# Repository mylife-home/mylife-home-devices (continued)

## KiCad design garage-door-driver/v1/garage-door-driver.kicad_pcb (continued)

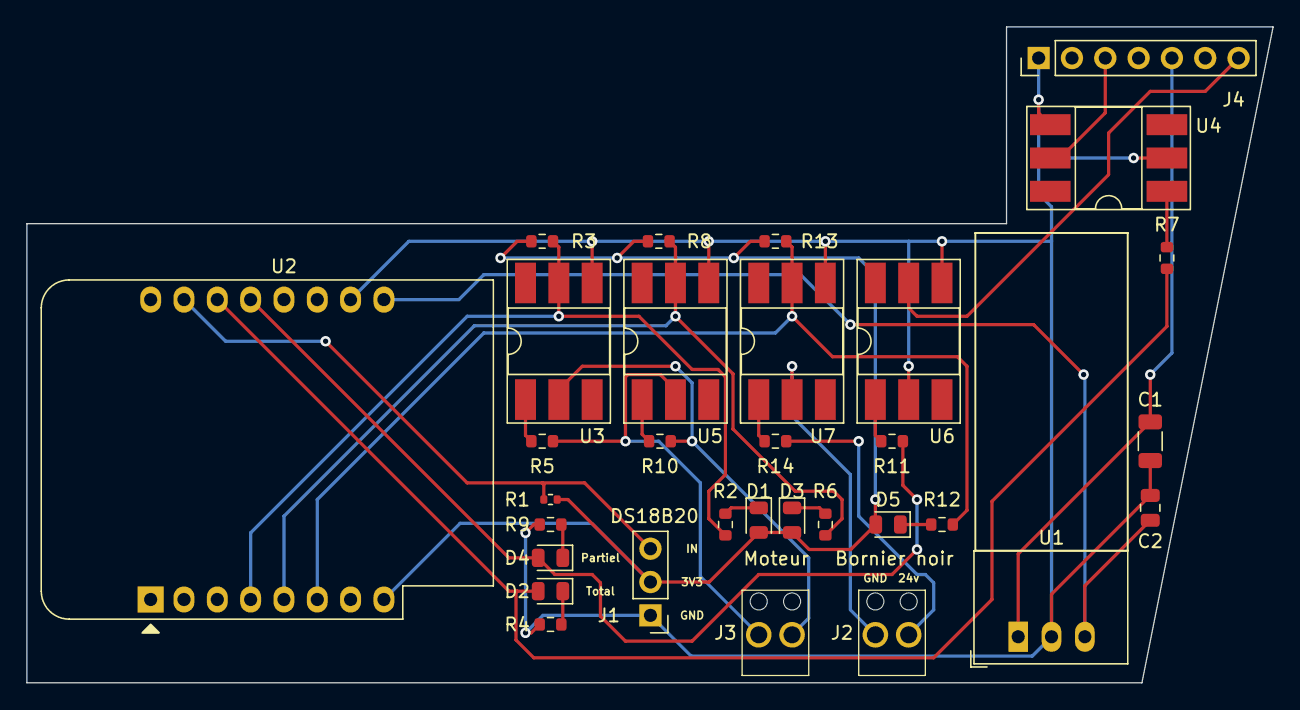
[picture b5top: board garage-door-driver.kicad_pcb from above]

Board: 2 copper layers, 95.0 x 50.0 mm, 32 parts (0 on the bottom side), 26 nets.

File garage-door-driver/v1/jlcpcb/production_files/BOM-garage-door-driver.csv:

Comment,Designator,Footprint,LCSC
2.2KΩ,"R10,R14,R5",R_0603_1608Metric,C176136
1KΩ,"R12,R2,R4,R6,R9",R_0603_1608Metric,C21190
220Ω,"R11,R7",R_0603_1608Metric,C22962
LED,"D1,D2,D3,D4,D5",D_0805_2012Metric,C2297
10KΩ,"R13,R3,R8",R_0603_1608Metric,C25804
4.7KΩ,R1,R_0402_1005Metric,C25900
10μF/50V,C1,C_1206_3216Metric,C417124
4N35,"U3,U4,U5,U6,U7",DIP-6_W8.89mm_SMDSocket_LongPads,C500385
22μF/10V,C2,C_0805_2012Metric,C92814
Conn_01x03_Male,J1,PinHeader_1x03_P2.54mm_Vertical,
WeMos_D1_mini,U2,WEMOS_D1_mini_light,
Conn_01x07_Pin,J4,PinHeader_1x07_P2.54mm_Vertical,
Screw_Terminal_01x02,J2,RS PRO Terminal Small x2,
R-785.0-1.0,U1,Converter_DCDC_RECOM_R-78E-0.5_THT,
Screw_Terminal_01x02,J3,RS PRO Terminal Small x2,

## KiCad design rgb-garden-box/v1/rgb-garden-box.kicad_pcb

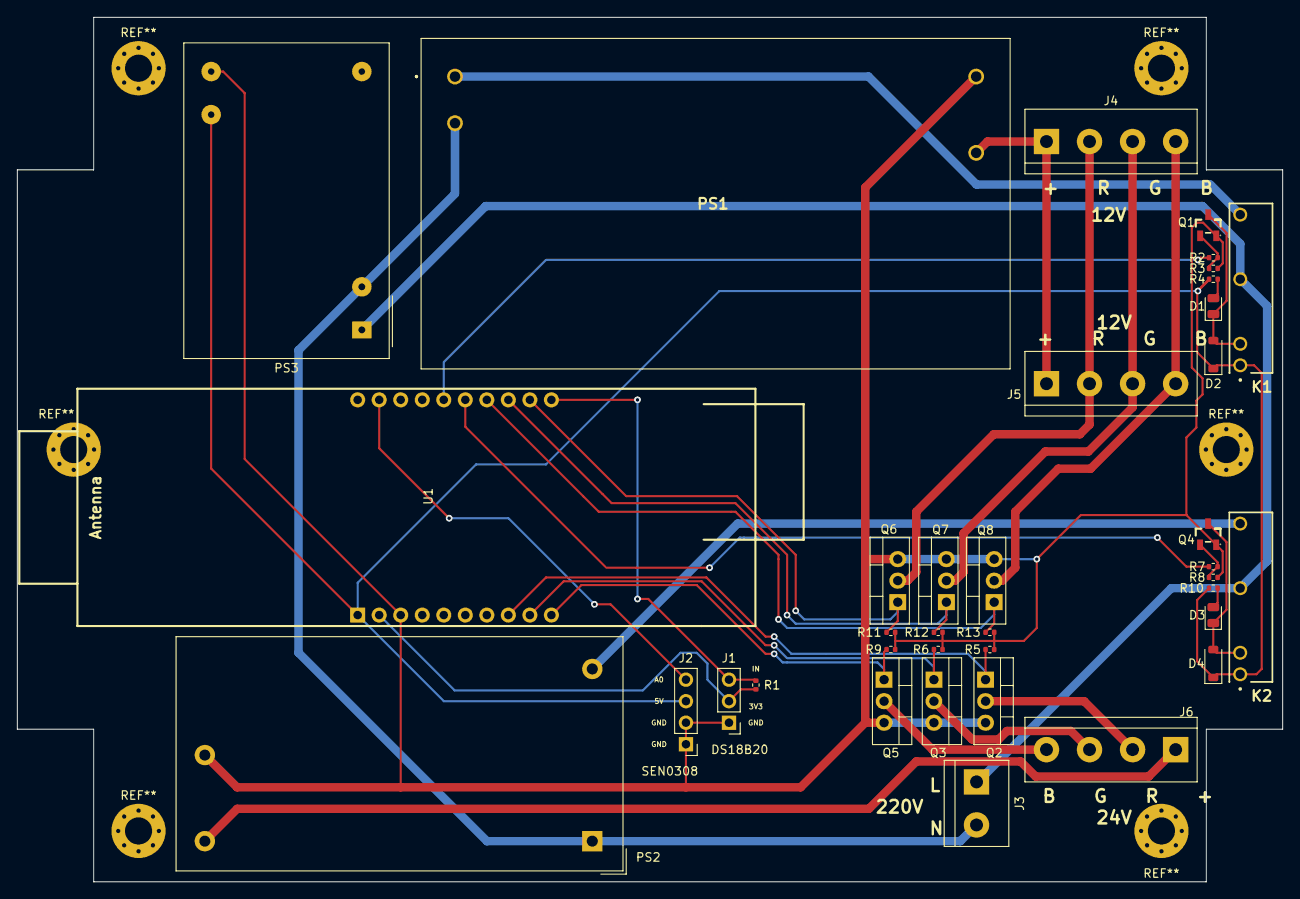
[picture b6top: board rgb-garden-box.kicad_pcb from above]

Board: 2 copper layers, 149.3 x 102.0 mm, 37 parts (0 on the bottom side), 31 nets.

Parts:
D1, D3: LED; D_0805_2012Metric
D2, D4: 1N4148; D_SOD-123
J1: Conn_01x03_Male; PinHeader_1x03_P2.54mm_Vertical
J2: Conn_01x04_Male; PinHeader_1x04_P2.54mm_Vertical
J3: Screw_Terminal_01x02; TerminalBlock_bornier-2_P5.08mm
J4, J5, J6: Screw_Terminal_01x04; TerminalBlock_bornier-4_P5.08mm
K1, K2: G6DN-1A-L_DC5; G6DN-1A-L
PS1: Mean Well 12V 2.5A (30W); IRM-30-12
PS2: RS PRO 24V 833mA (20W); RS PRO Alim 5V 2A
PS3: Alim RS PRO 5V 1A; Converter_ACDC_MeanWell_IRM-03-xx_THT
Q1, Q4: 2N3904; SOT-23-3_L2.9-W1.3-P1.90-LS2.4-TR
Q2, Q3, Q5, Q6, Q7, Q8: IRLZ44N; TO-220-3_Vertical
R1: 4.7KΩ; R_0402_1005Metric
R2, R4, R7, R10: 1KΩ; R_0402_1005Metric
R3, R5, R6, R8, R9, R11, R12, R13: 10KΩ; R_0402_1005Metric
U1: ESP32-POE

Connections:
+3V3: J1.2, R1.1, U1.2 (+3.3V_(out))
+5V: D2.1 (K), D4.1 (K), J2.3, K1.1, K2.1, PS3.16 (+Vo), R4.1, R10.1, U1.1 (+5V)
+12V: J4.1, J5.1, PS1.3 (+Vout)
+24V: J6.1, PS2.4 (+Vo)
GND: J1.1, J2.1, J2.2, PS1.4 (-Vout), PS2.3 (-Vo), PS3.14 (-Vo), Q1.1 (E), Q2.3 (S), Q3.3 (S), Q4.1 (E), Q5.3 (S), Q6.3 (S), Q7.3 (S), Q8.3 (S), R3.2, R5.2, R6.2, R8.2, R9.2, R11.2, R12.2, R13.2, U1.3 (GND)
unnamed: D1.2 (A), R4.2
unnamed: D1.1 (K), D2.2 (A), K1.2, Q1.3 (C)
unnamed: D3.2 (A), R10.2
unnamed: D3.1 (K), D4.2 (A), K2.2, Q4.3 (C)
unnamed: J1.3, R1.2, U1.11 (GPIO13)
unnamed: J2.4, U1.19 (GPIO36)
unnamed: J3.1, K1.5, K2.5, PS3.1 (AC/L)
unnamed: J3.2, PS1.2 (AC/N), PS2.1 (AC/N), PS3.3 (AC/N)
unnamed: J4.2, J5.2, Q6.2 (D)
unnamed: J4.3, J5.3, Q7.2 (D)
unnamed: J4.4, J5.4, Q8.2 (D)
unnamed: J6.2, Q2.2 (D)
unnamed: J6.3, Q3.2 (D)
unnamed: J6.4, Q5.2 (D)
unnamed: K1.8, PS1.1 (AC/L)
unnamed: K2.8, PS2.2 (AC/L)
unnamed: Q1.2 (B), R2.1, R3.1
unnamed: Q2.1 (G), R5.1, U1.8 (GPIO3)
unnamed: Q3.1 (G), R6.1, U1.9 (GPIO4)
unnamed: Q4.2 (B), R7.1, R8.1
unnamed: Q5.1 (G), R9.1, U1.10 (GPIO5)
unnamed: Q6.1 (G), R11.1, U1.12 (GPIO14)
unnamed: Q7.1 (G), R12.1, U1.13 (GPIO15)
unnamed: Q8.1 (G), R13.1, U1.14 (GPIO16)
unnamed: R7.2, U1.15 (GPIO32)
unnamed: R2.2, U1.16 (GPIO33)

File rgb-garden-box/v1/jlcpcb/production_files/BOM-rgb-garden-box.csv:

Comment,Designator,Footprint,LCSC
1KΩ,"R10,R2,R4,R7",R_0402_1005Metric,C11702
2N3904,"Q1,Q4",SOT-23-3_L2.9-W1.3-P1.90-LS2.4-TR,C18536
LED,"D1,D3",D_0805_2012Metric,C2297
10KΩ,"R11,R12,R13,R3,R5,R6,R8,R9",R_0402_1005Metric,C25744
4.7KΩ,R1,R_0402_1005Metric,C25900
1N4148,"D2,D4",D_SOD-123,C81598
IRLZ44N,Q8,TO-220-3_Vertical,
IRLZ44N,Q7,TO-220-3_Vertical,
IRLZ44N,Q6,TO-220-3_Vertical,
IRLZ44N,Q5,TO-220-3_Vertical,
IRLZ44N,Q3,TO-220-3_Vertical,
IRLZ44N,Q2,TO-220-3_Vertical,
G6DN-1A-L_DC5,K1,G6DN-1A-L,
Screw_Terminal_01x04,J5,TerminalBlock_bornier-4_P5.08mm,
Screw_Terminal_01x04,J6,TerminalBlock_bornier-4_P5.08mm,
Mean Well 12V 2.5A (30W),PS1,IRM-30-12,
G6DN-1A-L_DC5,K2,G6DN-1A-L,
Conn_01x03_Male,J1,PinHeader_1x03_P2.54mm_Vertical,
Screw_Terminal_01x04,J4,TerminalBlock_bornier-4_P5.08mm,
Screw_Terminal_01x02,J3,TerminalBlock_bornier-2_P5.08mm,
RS PRO 24V 833mA (20W),PS2,RS PRO Alim 5V 2A,
ESP32-POE,U1,ESP32-POE,
Alim RS PRO 5V 1A,PS3,Converter_ACDC_MeanWell_IRM-03-xx_THT,
Conn_01x04_Male,J2,PinHeader_1x04_P2.54mm_Vertical,

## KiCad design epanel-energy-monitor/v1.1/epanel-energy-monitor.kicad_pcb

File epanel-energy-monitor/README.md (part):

# ePanel Energy Monitor

## Besoin

- 12 capteurs
  - abonnement 12KVA ~ 55A
  - 4 sur inter diff (entre 40A et 63A)
  - 8 sur disjoncteurs (entre 10A et 32A)
- teleinfo

## Design

- MCP3208 x2
- déplacer ESP dans un boitier DIN a part

### Matériel

- Boîtier : 
  - https://fr.rs-online.com/web/p/boitiers-rail-din/7495837
  - https://fr.farnell.com/camdenboss/cnmb-6-kit/boitier-rail-din-m6/dp/3954259
- Borniers :
  - Petits : https://fr.rs-online.com/web/p/borniers-pour-circuits-imprimes/7901098
  - Grands : https://fr.rs-online.com/web/p/borniers-pour-circuits-imprimes/1444286
- Selecteurs : 
  - https://fr.rs-online.com/web/p/interrupteurs-dip-de-codage-rotatif/1796751
  - https://fr.farnell.com/nidec-copal/ss-10-15spe/commut-rotatif-sp5t-0-1a-5vdc/dp/2854806
- Câble 2x4 : https://www.amazon.fr/sourcing-map-Connecteur-Broche-Femelle/dp/B07H26VF1J
- Transfo : https://fr.rs-online.com/web/p/transformateurs-pour-circuits-imprimes/7320525
-  CT Clamp Schneider:
  - https://www.amazon.fr/Transformateurs-courant-ferm%C3%A9s-80a-Lot/dp/B01G5M1MT4
  - https://www.se.com/fr/fr/product/EER39200/wiser-energy-lot-de-5-tc-transformateurs-de-courant-ferm%C3%A9s-80a/

## V1.1

### Réglages

- pos1 = 220Ω = 10A
- pos2 = 120Ω = 16A
- pos3 = 100Ω = 20A
- pos4 =  62Ω = 32A
- pos5 =  33Ω = 60A

### 3D view

### Main

### CT Sensor

### Images

| | | |
|---|---|---|
||||
||||
||||

### Notes:

- plus de résistances 200Ω en stock, donc remplacement par une 220Ω. L'intensité max pour 10A pass de 10.5 à 9.5

## V1

### Réglages

- pos1 = 200Ω = 10A
- pos2 = 120Ω = 16A
- pos3 = 100Ω = 20A
- pos4 =  62Ω = 32A
- pos5 =  33Ω = 60A

### 3D view

### Main

### CT Sensor

### TODO

- OK LTV-814 : mauvais footprint, le bon est plus "écarté", cf jlcpcb/parts
- OK BSS138: mauvais pinout/footprint, cf jlcpcb/parts
- OK borniers pour CT plus petits (2.54 ecartement) -> https://fr.rs-online.com/web/p/borniers-pour-circuits-imprimes/7901098
- OK transfo: pastilles bien placées mais trop petites
- OK transfo: ajouter des pin headers sur secondaire pour facilement pouvoir mesurer la tension au voltmetre
- OK Au lieu de jumpers pour config resistances, mettre un commutateur rotatif :
  - https://fr.rs-online.com/web/p/interrupteurs-dip-de-codage-rotatif/1796751
  - https://fr.farnell.com/nidec-copal/ss-10-15spe/commut-rotatif-sp5t-0-1a-5vdc/dp/2854806
- Note: Boitier DIN : Largeur espace pour bornier : 1.3cm
- OK ajouter une led pour montrer qu'il est bien alimenté

### Bugs

- pinout SS-10 KO !!!
```
1 pos3       5 NC
2 pos2       6 C
3 C          7 pos5
4 pos1       8 pos4
```
Note: le point correspond à l'angle rogné sur le SS-10

- pinout bornier inversé : les trous sont du côté des cables

## Prototype-1

### Tests

### Observations

- Teleinfo
  - mauvais composant pour optocoupleur :
    - courant LTV-8141
    - correct: LTV-814 (C125118)
  - voir si on doit mettre une résistance de 4.7K, 1.2K ou 1K
- CT Clamp
  - les prises jack a souder sont très peu épaisses, elles doivent être au board du PCB ou changer de modèle
  - test avec aspirateur:
    - Théoriquement: 1300W /230V = 5.6A
    - Mesure avec ampèremètre sur directement sur le courant secteur : 6.12A
    - Mesure avec voltmètre aux bornes du burden resistor 120ohm : 0.31V /120Rb *2000 = 5.16A
    - Mesure avec oem_clamp recodé : 7.55A à l'allumage puis 6.35A après (instable). Note : le 0 est à 0.06A

### A faire pour proto 2:

- TIC
  - LTV-814
  - plusieurs choix de résistances pour TIC : 1k, 1.2k, 2k, 3.3k, 4.7k
  - mettre des pins headers pour pouvoir mesurer a l'oscillo si problème
- CT Clamp
  - mettre un MCP3208
  - jumper pour passer soit par MCP3208 soit direct sur ESP32
  - attention: GPIO2 et GPIO4 ne semble pas etre valides pour ADC avec esphome. GPIO32 et GPIO33 oui
  - mettre des pins headers pour pouvoir mesurer au voltmètre
  - plusieurs burden possibles:
    - 10A 233ohm -> 220 (10.6A)
    - 16A 146ohm -> 150 (15.6A)
    - 20A 117ohm -> 120 (19.4A)
    - 32A 73ohm -> 75 (31.1A)
    - 60A 39ohm -> 33 (70.7A)
- test emplacement ESP32
  - avec le connecteur ethernet vers le bas
  - sur la partie droite, mais pas collé (sinon les ergo vont gener)
  - au milieu en hauteur
  - on decoupera le boitier au dremel pour faire la place pour le connecteur ethernet

## Prototype-2

### Tests

- CT Clamp avec ADC ESP32 - Burden 220ohm (10A) sur sèche cheveux 1500W
  - eteint : 0.030A - 0.036A
  - level1 : 2.321A - 2.323A = 533W
  - level3 : 6.395A - 6.431A = 1470W - 1479W

- CT Clamp avec MCP3008 - Burden 220ohm (10A) sur sèche cheveux 1500W
  - eteint : 0.043A - 0.105A
  - level1 : 2.316A = 532.68W
  - level3 : 6.335A = 1457W

- CT Clamp avec MCP3008 - Burden 75ohm (32A) sur SPA
  - au "repos" : 0.117A - 0.258A -> 26,91W - 59,34W
  - filtration? : 0.551A -> 126,73W
  - au "travail" (chauffage ?) : 11.751A -> 2700W

- CT Clamp comparaison avec Schneider avec MCP3008 - Burden 75ohm sur sèche cheveux 1500W - level3
  - Mesure avec CT clamp YHDC : 6.3 - 6.4
  - Mesure avec multimetre : 6.36
  - Mesure schneider config 1600 turns => 5.6
  - Mesure schneider config 2000 turns => 7
  => en faisant le ratio, CT clamp Schneider = 1800 turns

- CT Clamp comparaison avec Schneider avec MCP3008 - Burden 75ohm sur ampoule 40W
  - Mesure schneider config 1800 turns : 0.27
  - Mesure schneider config 1600 turns : 0.24
  - Mesure avec multimetre : 0.15
  - 40W = 0.17
  => en faisant le ratio, CT clamp Shneider = 1000 turns => tres peut precis, mais 0.27A sur 32A < 1%

- CT Clamp comparaison avec Schneider avec MCP3008 - Burden 220ohm sur ampoule 40W
  - Mesure schneider config 1800 turns : 0.18
  - Mesure avec multimetre : 0.15
  - 40W = 0.17

### Observations

- Teleinfo
  - ne fonctionne pas
  - WeMos TIC fonctionne, schematic : https://cdn.tindiemedia.com/images/resize/s_ZnNZRPrxDSvn3I8rBo9nkt9-8=/p/fit-in/1370x912/filters:fill(fff)/i/5857/products/2021-11-24T17%3A07%3A47.675Z-WeMos-TIC-sch.png?1637747448
  - Note : les valeurs des resistances correspondent bien au schematic
- CT Clamp MCP3008
  - GPIO15 = strapping pin
  - rajouter Voltage sensor pour pouvoir calculer la puissance réelle
    - https://learn.openenergymonitor.org/electricity-monitoring/voltage-sensing/measuring-voltage-with-an-acac-power-adapter
    - https://fr.rs-online.com/web/p/transformateurs-pour-circuits-imprimes/1213819
  - tester reactivité ESP32 avec 16 mesures (meme si pas de CT clamp, juste pour etre sur que ca ne perde pas en reactivite)
  - trouver des CT Clamp plus petits ? comme ceux de Schneider ?
    - ceux de Schneider:
      - https://www.amazon.fr/Transformateurs-courant-ferm%C3%A9s-80a-Lot/dp/B01G5M1MT4
      - https://www.se.com/fr/fr/product/EER39200/wiser-energy-lot-de-5-tc-transformateurs-de-courant-ferm%C3%A9s-80a/
      - semble etre 80A:50mA => en fait 1800 turns
      - tore d'une seule pièce
  - faire une sortie screwterminal a cote du jack pour pouvoir tester d'autres CT Clamp
  - burdens:
    - essayer d'optimiser les valeurs en pouvant les mettre en //
    - attention : schneider CT turns = 1800, YHDC CT turns = 2000
- Montage ESP32 dans DIN box
  - trop sur le côté, décaler de 2-3mm vers le milieu
  - la prochaine fois faire un truc moins cochon au Dremel
- Montage prises Jack
  - l'emplacement est parfait, mais on ne peut pas en mettre de chaque coté de la board et la faire rentrer dans le boitiers car ils depassent

### A faire pour proto 3

- Teleinfo
  - doit fonctionner
  - ajouter une led
- CT Clamp
  - ajouter un ADS1115 pour tester la difference de précision, avec un autre switch
    - datasheet : https://www.ti.com/lit/ds/symlink/ads1115.pdf
    - avec un burden pour 60A et la precision de l'ADC, cela suffit peut etre sans burden en plus ?
  - ajouter capteur de tension
    - Transfo : 6V -> https://fr.rs-online.com/web/p/transformateurs-pour-circuits-imprimes/7320525
    - no load voltage = x1.8 => 10.8V RMS
    - https://learn.openenergymonitor.org/electricity-monitoring/voltage-sensing/measuring-voltage-with-an-acac-power-adapter
    - 10.8V RMS
    - = 15.3V peak
    - = 30,6V peak-peak
    - ratio: 12 / (100 + 12) = 0,107
    - = 3.274V peak-peak
  - ajouter ampli op
    - https://learn.openenergymonitor.org/electricity-monitoring/ctac/acac-buffered-voltage-bias
    - pour chaque capteur, switch ampli op ou pont diviseur
  - mettre plusieurs capteurs de courant pour etre sur que l'ampli op fonctionne pour plusieurs, eg : 3 capteurs CT + 1 tension
  - mettre des terminalscrews au lieu des jacks pour tester CT Schneider
  - jeu de burden resistances pour CT turns 1800
    - 10A 210ohm -> 200 (10.5A)
    - 16A 131ohm -> 130 (16.2A)
    - 20A 105ohm -> 100 (21A)
    - 32A 66ohm -> 62 (33.9A)
    - 60A 35ohm -> 33 (63.6A)
  - tester avec vraie alim (pour tester la stabilité des mesures avec l'alim)
  - diodes pour protéger les ADC : https://openenergymonitor.github.io/forum-archive/sites/default/files/MyInputCircuits_0.jpg
    - ADS a deja des protections dans son MUX
  - pour chaque capteur, switch ADS vs MCP vs ESP
- Montage ESP32
  - corriger l'emplacement sur la board

## Prototype-3

### Tests

- Sortie transfo mesurée :
  - (7.5VRMS)
  - 8.8V RMS

- MCP/OP (seche cheveux sur ct1)

```
[09:39:28][D][oem_computer:065]: 'ct2' - v_rms=234.4V, i_rms=0.052A, p_real=0.3W (sample count: 1025, sample per period: 102.50)
[09:39:28][D][sensor:127]: 'epanel-ct2-current': Sending state 0.05180 A with 2 decimals of accuracy
[09:39:28][D][sensor:127]: 'epanel-ct2-voltage': Sending state 234.41190 V with 0 decimals of accuracy
[09:39:28][D][sensor:127]: 'epanel-ct2-apparent-power': Sending state 12.14348 VA with 0 decimals of accuracy
[09:39:28][D][sensor:127]: 'epanel-ct2-real-power': Sending state 0.34598 W with 0 decimals of accuracy
[09:39:29][D][oem_computer:065]: 'ct1' - v_rms=234.9V, i_rms=5.399A, p_real=-989.3W (sample count: 1046, sample per period: 104.60)
[09:39:29][D][sensor:127]: 'epanel-ct1-current': Sending state 5.39941 A with 2 decimals of accuracy
[09:39:29][D][sensor:127]: 'epanel-ct1-voltage': Sending state 234.88547 V with 0 decimals of accuracy
[09:39:29][D][sensor:127]: 'epanel-ct1-apparent-power': Sending state 1268.24182 VA with 0 decimals of accuracy
[09:39:29][D][sensor:127]: 'epanel-ct1-real-power': Sending state -989.25970 W with 0 decimals of accuracy
[09:39:30][D][oem_computer:065]: 'ct3' - v_rms=235.3V, i_rms=0.050A, p_real=0.0W (sample count: 1055, sample per period: 105.50)
[09:39:30][D][sensor:127]: 'epanel-ct3-current': Sending state 0.04952 A with 2 decimals of accuracy
[09:39:30][D][sensor:127]: 'epanel-ct3-voltage': Sending state 235.33501 V with 0 decimals of accuracy
[09:39:30][D][sensor:127]: 'epanel-ct3-apparent-power': Sending state 11.65409 VA with 0 decimals of accuracy
[09:39:30][D][sensor:127]: 'epanel-ct3-real-power': Sending state 0.02975 W with 0 decimals of accuracy

[09:39:38][D][oem_computer:065]: 'ct2' - v_rms=234.8V, i_rms=0.047A, p_real=0.5W (sample count: 1032, sample per period: 103.20)
[09:39:38][D][sensor:127]: 'epanel-ct2-current': Sending state 0.04736 A with 2 decimals of accuracy
[09:39:38][D][sensor:127]: 'epanel-ct2-voltage': Sending state 234.82834 V with 0 decimals of accuracy
[09:39:38][D][sensor:127]: 'epanel-ct2-apparent-power': Sending state 11.12200 VA with 0 decimals of accuracy
[09:39:38][D][sensor:127]: 'epanel-ct2-real-power': Sending state 0.52791 W with 0 decimals of accuracy
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
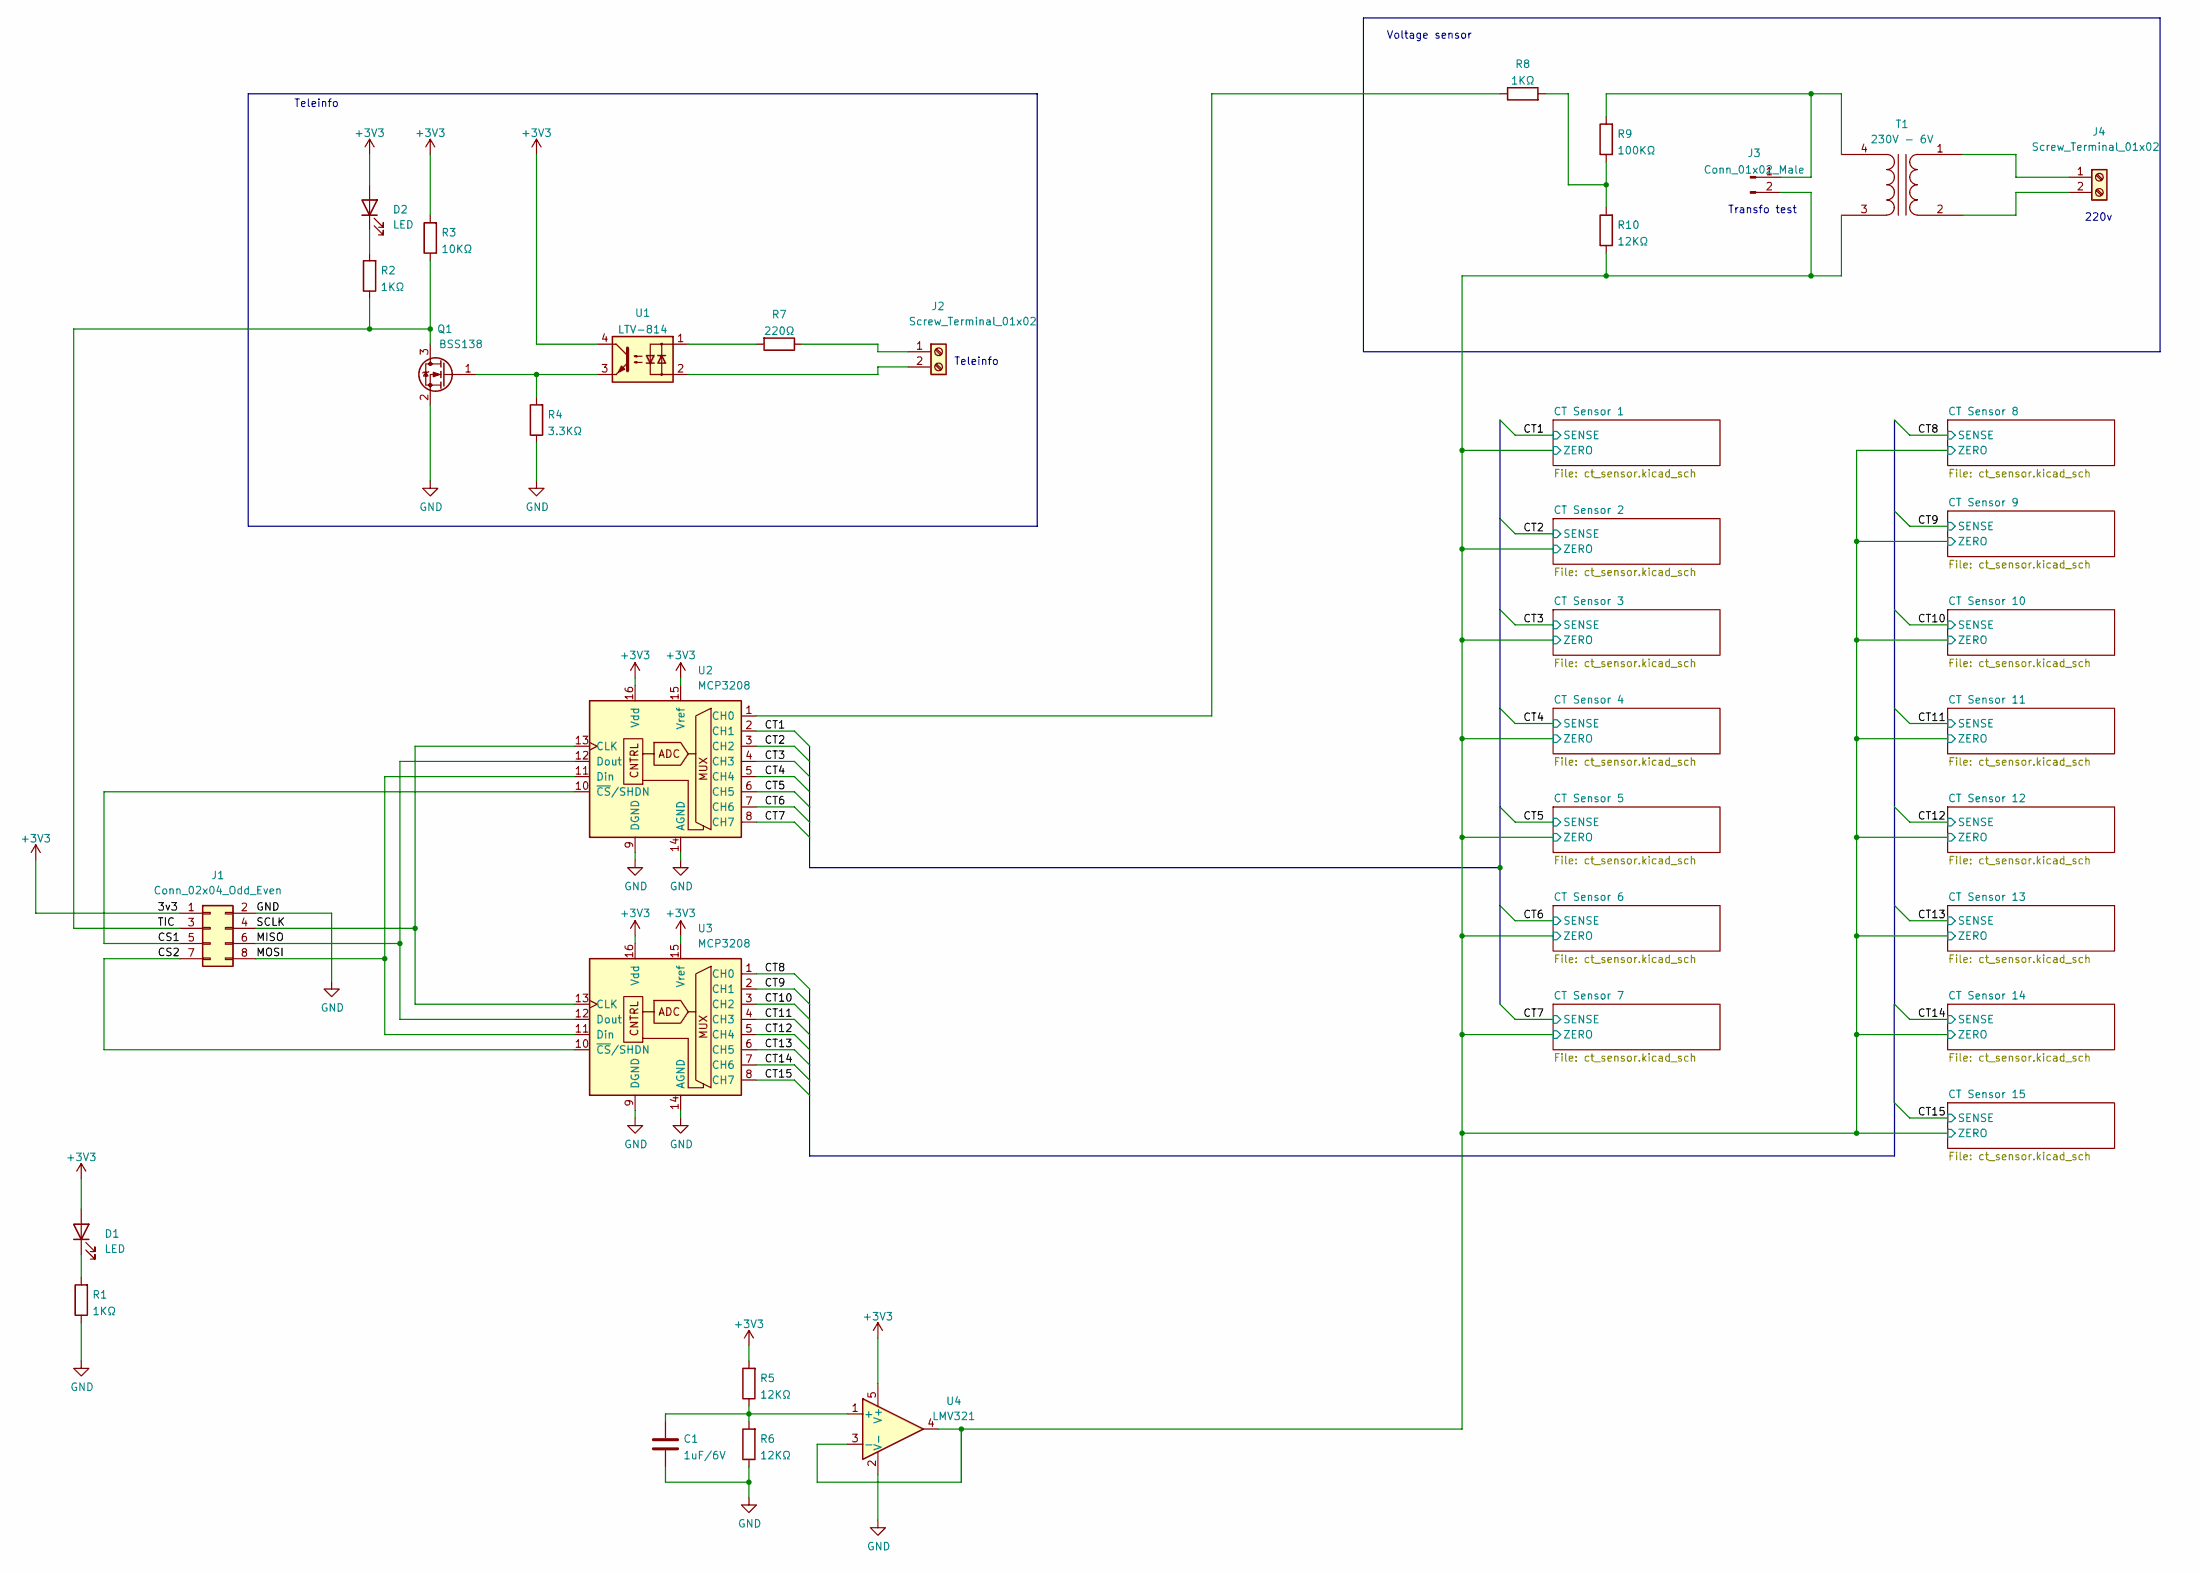
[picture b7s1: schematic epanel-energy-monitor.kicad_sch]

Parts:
C1: 1uF/6V; R_0603_1608Metric; LCSC C15849
D1, D2: LED; D_0805_2012Metric; LCSC C2297
J1: Conn_02x04_Odd_Even; PinHeader_2x04_P2.54mm_Vertical
J2: Screw_Terminal_01x02; RS PRO Terminal Small x2
J3: Conn_01x02_Male; PinHeader_1x02_P2.54mm_Vertical
J4: Screw_Terminal_01x02; TerminalBlock_bornier-2_P5.08mm
Q1: BSS138; SOT-23; LCSC C2938375
R1, R2, R8: 1KΩ; R_0603_1608Metric; LCSC C21190
R3: 10KΩ; R_0603_1608Metric; LCSC C25804
R4: 3.3KΩ; R_0603_1608Metric; LCSC C22978
R5, R6, R10: 12KΩ; R_0603_1608Metric; LCSC C22790
R7: 220Ω; R_0603_1608Metric; LCSC C22962
R9: 100KΩ; R_0603_1608Metric; LCSC C25803
T1: 230V - 6V; RS PRO Transfo 6V 0.35VA
U1: LTV-814; SMDIP-4_W9.53mm; LCSC C125118
U2, U3: MCP3208; SOIC-16_3.9x9.9mm_P1.27mm; LCSC C16939
U4: LMV321; SOT-23-5; LCSC C7972

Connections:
+3V3: D1.2 (A), D2.2 (A), J1.1, R3.2, R5.2, U1.4, U2.15 (Vref), U2.16 (Vdd), U3.15 (Vref), U3.16 (Vdd), U4.5 (V+)
/CS1: J1.5, U2.10 (~CS/SHDN)
/CS2: J1.7, U3.10 (~CS/SHDN)
/CT1: U2.2 (CH1); also elsewhere on the board
/CT2: U2.3 (CH2); also elsewhere on the board
/CT3: U2.4 (CH3); also elsewhere on the board
/CT4: U2.5 (CH4); also elsewhere on the board
/CT5: U2.6 (CH5); also elsewhere on the board
/CT6: U2.7 (CH6); also elsewhere on the board
/CT7: U2.8 (CH7); also elsewhere on the board
/CT8: U3.1 (CH0); also elsewhere on the board
/CT9: U3.2 (CH1); also elsewhere on the board
/CT10: U3.3 (CH2); also elsewhere on the board
/CT11: U3.4 (CH3); also elsewhere on the board
/CT12: U3.5 (CH4); also elsewhere on the board
/CT13: U3.6 (CH5); also elsewhere on the board
/CT14: U3.7 (CH6); also elsewhere on the board
/CT15: U3.8 (CH7); also elsewhere on the board
/CT Sensor 1/ZERO: J3.2, R10.1, T1.3 (SA), U4.3 (-), U4.4; also elsewhere on the board
/MISO: J1.6, U2.12 (Dout), U3.12 (Dout)
/MOSI: J1.8, U2.11 (Din), U3.11 (Din)
/SCLK: J1.4, U2.13 (CLK), U3.13 (CLK)
/TIC: J1.3, Q1.3 (D), R2.1, R3.1
GND: C1.2, J1.2, Q1.2 (S), R1.1, R4.1, R6.1, U2.9 (DGND), U2.14 (AGND), U3.9 (DGND), U3.14 (AGND), U4.2 (V-)
unnamed: D1.1 (K), R1.2
unnamed: D2.1 (K), R2.2
unnamed: J2.1, R7.1
unnamed: J2.2, U1.2
unnamed: J3.1, R9.2, T1.4 (SB)
unnamed: J4.1, T1.1 (AA)
unnamed: J4.2, T1.2 (AB)
unnamed: Q1.1 (G), R4.2, U1.3
unnamed: R7.2, U1.1
unnamed: R8.2, R9.1, R10.2
unnamed: R8.1, U2.1 (CH0)
unnamed: C1.1, R5.1, R6.2, U4.1 (+)

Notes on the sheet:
Teleinfo
Transfo test
220v
Voltage sensor

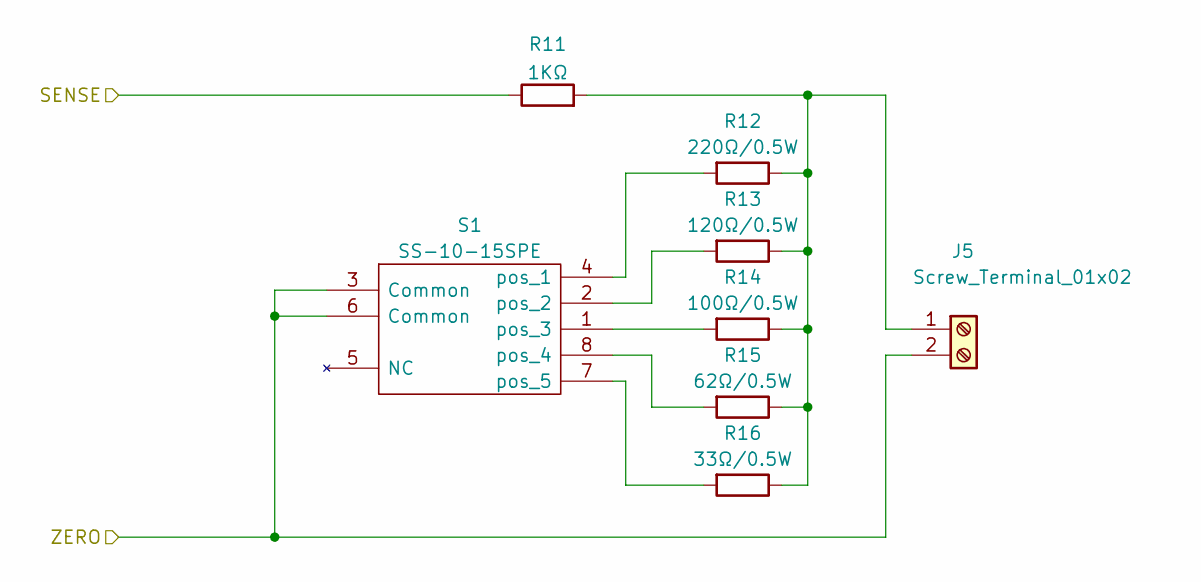
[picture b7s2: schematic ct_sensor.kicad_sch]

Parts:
J5: Screw_Terminal_01x02; RS PRO Terminal Small x2
R11: 1KΩ; R_0603_1608Metric; LCSC C21190
R12: 220Ω/0.5W; R_0805_2012Metric; LCSC C966130
R13: 120Ω/0.5W; R_0805_2012Metric; LCSC C543533
R14: 100Ω/0.5W; R_0805_2012Metric; LCSC C417003
R15: 62Ω/0.5W; R_0805_2012Metric; LCSC C560547
R16: 33Ω/0.5W; R_0805_2012Metric; LCSC C560522
S1: SS-10-15SPE; RS PRO SS-10-15SPE; Manufacturer_Part_Number SS-10-15SPE

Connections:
/CT1: R11.1; also elsewhere on the board
/CT Sensor 1/ZERO: J5.2, S1.3 (Common), S1.6 (Common); also elsewhere on the board
unnamed: J5.1, R11.2, R12.1, R13.1, R14.1, R15.1, R16.1
unnamed: R12.2, S1.4 (pos_1)
unnamed: R13.2, S1.2 (pos_2)
unnamed: R14.2, S1.1 (pos_3)
unnamed: R15.2, S1.8 (pos_4)
unnamed: R16.2, S1.7 (pos_5)

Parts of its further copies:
J6, J7, J8, J9, J10, J11, J12, J13, J14, J15, J16, J17, J18, J19: Screw_Terminal_01x02; RS PRO Terminal Small x2
R17, R23, R29, R35, R41, R47, R53, R59, R65, R71, R77, R83, R89, R95: 1KΩ; R_0603_1608Metric; LCSC C21190
R18, R24, R30, R36, R42, R48, R54, R60, R66, R72, R78, R84, R90, R96: 220Ω/0.5W; R_0805_2012Metric; LCSC C966130
R19, R25, R31, R37, R43, R49, R55, R61, R67, R73, R79, R85, R91, R97: 120Ω/0.5W; R_0805_2012Metric; LCSC C543533
R20, R26, R32, R38, R44, R50, R56, R62, R68, R74, R80, R86, R92, R98: 100Ω/0.5W; R_0805_2012Metric; LCSC C417003
R21, R27, R33, R39, R45, R51, R57, R63, R69, R75, R81, R87, R93, R99: 62Ω/0.5W; R_0805_2012Metric; LCSC C560547
R22, R28, R34, R40, R46, R52, R58, R64, R70, R76, R82, R88, R94, R100: 33Ω/0.5W; R_0805_2012Metric; LCSC C560522
S2, S3, S4, S5, S6, S7, S8, S9, S10, S11, S12, S13, S14, S15: SS-10-15SPE; RS PRO SS-10-15SPE; Manufacturer_Part_Number SS-10-15SPE

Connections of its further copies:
/CT2: R17.1; also elsewhere on the board
/CT3: R23.1; also elsewhere on the board
/CT4: R29.1; also elsewhere on the board
/CT5: R35.1; also elsewhere on the board
/CT6: R41.1; also elsewhere on the board
/CT7: R47.1; also elsewhere on the board
/CT8: R53.1; also elsewhere on the board
/CT9: R59.1; also elsewhere on the board
/CT10: R65.1; also elsewhere on the board
/CT11: R71.1; also elsewhere on the board
/CT12: R77.1; also elsewhere on the board
/CT13: R83.1; also elsewhere on the board
/CT14: R89.1; also elsewhere on the board
/CT15: R95.1; also elsewhere on the board
/CT Sensor 1/ZERO: J6.2, J7.2, J8.2, J9.2, J10.2, J11.2, J12.2, J13.2, J14.2, J15.2, J16.2, J17.2, J18.2, J19.2, S2.3 (Common), S2.6 (Common), S3.3 (Common), S3.6 (Common), S4.3 (Common), S4.6 (Common), S5.3 (Common), S5.6 (Common), S6.3 (Common), S6.6 (Common), S7.3 (Common), S7.6 (Common), S8.3 (Common), S8.6 (Common), S9.3 (Common), S9.6 (Common), S10.3 (Common), S10.6 (Common), S11.3 (Common), S11.6 (Common), S12.3 (Common), S12.6 (Common), S13.3 (Common), S13.6 (Common), S14.3 (Common), S14.6 (Common), S15.3 (Common), S15.6 (Common); also elsewhere on the board
unnamed: J6.1, R17.2, R18.1, R19.1, R20.1, R21.1, R22.1
unnamed: J7.1, R23.2, R24.1, R25.1, R26.1, R27.1, R28.1
unnamed: J8.1, R29.2, R30.1, R31.1, R32.1, R33.1, R34.1
unnamed: J9.1, R35.2, R36.1, R37.1, R38.1, R39.1, R40.1
unnamed: J10.1, R41.2, R42.1, R43.1, R44.1, R45.1, R46.1
unnamed: J11.1, R47.2, R48.1, R49.1, R50.1, R51.1, R52.1
unnamed: J12.1, R53.2, R54.1, R55.1, R56.1, R57.1, R58.1
unnamed: J13.1, R59.2, R60.1, R61.1, R62.1, R63.1, R64.1
unnamed: J14.1, R65.2, R66.1, R67.1, R68.1, R69.1, R70.1
unnamed: J15.1, R71.2, R72.1, R73.1, R74.1, R75.1, R76.1
unnamed: J16.1, R77.2, R78.1, R79.1, R80.1, R81.1, R82.1
unnamed: J17.1, R83.2, R84.1, R85.1, R86.1, R87.1, R88.1
unnamed: J18.1, R89.2, R90.1, R91.1, R92.1, R93.1, R94.1
unnamed: J19.1, R95.2, R96.1, R97.1, R98.1, R99.1, R100.1
unnamed: R18.2, S2.4 (pos_1)
unnamed: R19.2, S2.2 (pos_2)
unnamed: R20.2, S2.1 (pos_3)
unnamed: R21.2, S2.8 (pos_4)
unnamed: R22.2, S2.7 (pos_5)
unnamed: R24.2, S3.4 (pos_1)
unnamed: R25.2, S3.2 (pos_2)
unnamed: R26.2, S3.1 (pos_3)
unnamed: R27.2, S3.8 (pos_4)
unnamed: R28.2, S3.7 (pos_5)
unnamed: R30.2, S4.4 (pos_1)
unnamed: R31.2, S4.2 (pos_2)
unnamed: R32.2, S4.1 (pos_3)
unnamed: R33.2, S4.8 (pos_4)
unnamed: R34.2, S4.7 (pos_5)
unnamed: R36.2, S5.4 (pos_1)
unnamed: R37.2, S5.2 (pos_2)
unnamed: R38.2, S5.1 (pos_3)
unnamed: R39.2, S5.8 (pos_4)
unnamed: R40.2, S5.7 (pos_5)
unnamed: R42.2, S6.4 (pos_1)
unnamed: R43.2, S6.2 (pos_2)
unnamed: R44.2, S6.1 (pos_3)
unnamed: R45.2, S6.8 (pos_4)
unnamed: R46.2, S6.7 (pos_5)
unnamed: R48.2, S7.4 (pos_1)
unnamed: R49.2, S7.2 (pos_2)
unnamed: R50.2, S7.1 (pos_3)
unnamed: R51.2, S7.8 (pos_4)
unnamed: R52.2, S7.7 (pos_5)
unnamed: R54.2, S8.4 (pos_1)
unnamed: R55.2, S8.2 (pos_2)
unnamed: R56.2, S8.1 (pos_3)
unnamed: R57.2, S8.8 (pos_4)
unnamed: R58.2, S8.7 (pos_5)
unnamed: R60.2, S9.4 (pos_1)
unnamed: R61.2, S9.2 (pos_2)
unnamed: R62.2, S9.1 (pos_3)
unnamed: R63.2, S9.8 (pos_4)
unnamed: R64.2, S9.7 (pos_5)
unnamed: R66.2, S10.4 (pos_1)
unnamed: R67.2, S10.2 (pos_2)
unnamed: R68.2, S10.1 (pos_3)
unnamed: R69.2, S10.8 (pos_4)
unnamed: R70.2, S10.7 (pos_5)
unnamed: R72.2, S11.4 (pos_1)
unnamed: R73.2, S11.2 (pos_2)
unnamed: R74.2, S11.1 (pos_3)
unnamed: R75.2, S11.8 (pos_4)
unnamed: R76.2, S11.7 (pos_5)
unnamed: R78.2, S12.4 (pos_1)
unnamed: R79.2, S12.2 (pos_2)
unnamed: R80.2, S12.1 (pos_3)
unnamed: R81.2, S12.8 (pos_4)
unnamed: R82.2, S12.7 (pos_5)
unnamed: R84.2, S13.4 (pos_1)
unnamed: R85.2, S13.2 (pos_2)
unnamed: R86.2, S13.1 (pos_3)
unnamed: R87.2, S13.8 (pos_4)
unnamed: R88.2, S13.7 (pos_5)
unnamed: R90.2, S14.4 (pos_1)
unnamed: R91.2, S14.2 (pos_2)
unnamed: R92.2, S14.1 (pos_3)
unnamed: R93.2, S14.8 (pos_4)
unnamed: R94.2, S14.7 (pos_5)
unnamed: R96.2, S15.4 (pos_1)
unnamed: R97.2, S15.2 (pos_2)
unnamed: R98.2, S15.1 (pos_3)
unnamed: R99.2, S15.8 (pos_4)
unnamed: R100.2, S15.7 (pos_5)

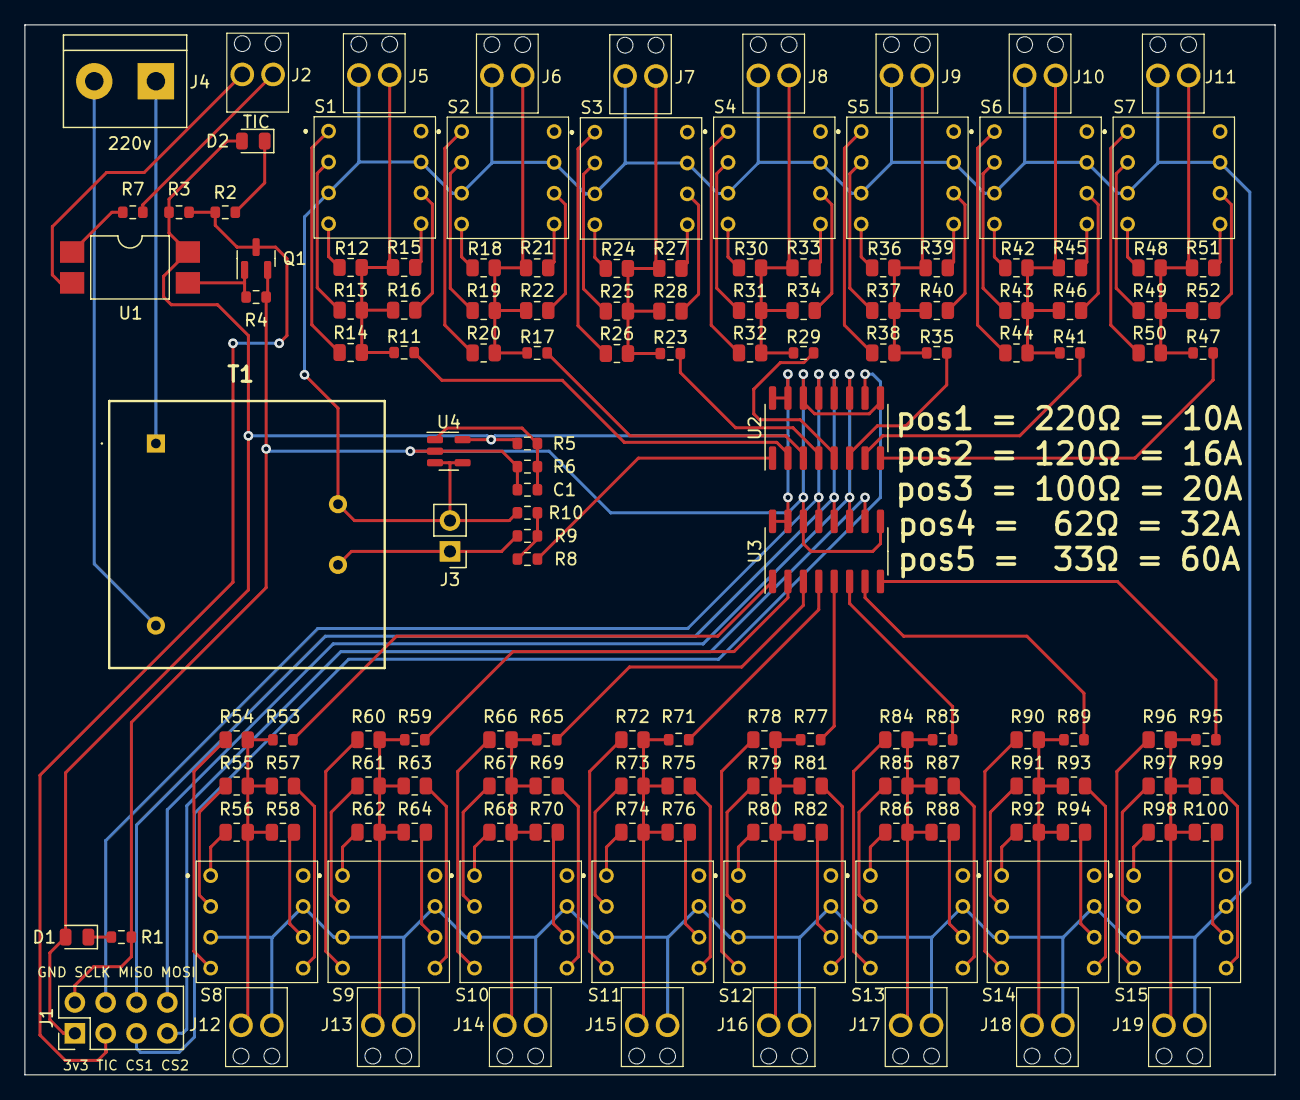
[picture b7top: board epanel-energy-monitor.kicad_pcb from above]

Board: 2 copper layers, 103.0 x 86.5 mm, 143 parts (0 on the bottom side), 126 nets.

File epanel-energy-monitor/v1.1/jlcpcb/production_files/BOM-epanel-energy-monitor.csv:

Comment,Designator,Footprint,LCSC
LTV-814,U1,SMDIP-4_W9.53mm,C125118
1uF/6V,C1,R_0603_1608Metric,C15849
MCP3208,"U2,U3",SOIC-16_3.9x9.9mm_P1.27mm,C16939
1KΩ,"R1,R11,R17,R2,R23,R29,R35,R41,R47,R53,R59,R65,R71,R77,R8,R83,R89,R95",R_0603_1608Metric,C21190
12KΩ,"R10,R5,R6",R_0603_1608Metric,C22790
220Ω,R7,R_0603_1608Metric,C22962
LED,"D1,D2",D_0805_2012Metric,C2297
3.3KΩ,R4,R_0603_1608Metric,C22978
100KΩ,R9,R_0603_1608Metric,C25803
10KΩ,R3,R_0603_1608Metric,C25804
BSS138,Q1,SOT-23,C2938375
100Ω/0.5W,"R14,R20,R26,R32,R38,R44,R50,R56,R62,R68,R74,R80,R86,R92,R98",R_0805_2012Metric,C417003
120Ω/0.5W,"R13,R19,R25,R31,R37,R43,R49,R55,R61,R67,R73,R79,R85,R91,R97",R_0805_2012Metric,C543533
33Ω/0.5W,"R100,R16,R22,R28,R34,R40,R46,R52,R58,R64,R70,R76,R82,R88,R94",R_0805_2012Metric,C560522
62Ω/0.5W,"R15,R21,R27,R33,R39,R45,R51,R57,R63,R69,R75,R81,R87,R93,R99",R_0805_2012Metric,C560547
LMV321,U4,SOT-23-5,C7972
220Ω/0.5W,"R12,R18,R24,R30,R36,R42,R48,R54,R60,R66,R72,R78,R84,R90,R96",R_0805_2012Metric,C966130
SS-10-15SPE,S15,RS PRO SS-10-15SPE,
Screw_Terminal_01x02,J15,RS PRO Terminal Small x2,
SS-10-15SPE,S12,RS PRO SS-10-15SPE,
SS-10-15SPE,S11,RS PRO SS-10-15SPE,
Screw_Terminal_01x02,J5,RS PRO Terminal Small x2,
Screw_Terminal_01x02,J6,RS PRO Terminal Small x2,
SS-10-15SPE,S6,RS PRO SS-10-15SPE,
Screw_Terminal_01x02,J2,RS PRO Terminal Small x2,
Screw_Terminal_01x02,J7,RS PRO Terminal Small x2,
SS-10-15SPE,S8,RS PRO SS-10-15SPE,
Screw_Terminal_01x02,J11,RS PRO Terminal Small x2,
SS-10-15SPE,S1,RS PRO SS-10-15SPE,
SS-10-15SPE,S5,RS PRO SS-10-15SPE,
Conn_02x04_Odd_Even,J1,PinHeader_2x04_P2.54mm_Vertical,
SS-10-15SPE,S3,RS PRO SS-10-15SPE,
SS-10-15SPE,S4,RS PRO SS-10-15SPE,
Screw_Terminal_01x02,J8,RS PRO Terminal Small x2,
Screw_Terminal_01x02,J9,RS PRO Terminal Small x2,
SS-10-15SPE,S7,RS PRO SS-10-15SPE,
SS-10-15SPE,S2,RS PRO SS-10-15SPE,
Screw_Terminal_01x02,J14,RS PRO Terminal Small x2,
Screw_Terminal_01x02,J16,RS PRO Terminal Small x2,
SS-10-15SPE,S13,RS PRO SS-10-15SPE,
SS-10-15SPE,S9,RS PRO SS-10-15SPE,
Conn_01x02_Male,J3,PinHeader_1x02_P2.54mm_Vertical,
Screw_Terminal_01x02,J4,TerminalBlock_bornier-2_P5.08mm,
SS-10-15SPE,S10,RS PRO SS-10-15SPE,
Screw_Terminal_01x02,J10,RS PRO Terminal Small x2,
Screw_Terminal_01x02,J17,RS PRO Terminal Small x2,
Screw_Terminal_01x02,J19,RS PRO Terminal Small x2,
Screw_Terminal_01x02,J12,RS PRO Terminal Small x2,
Screw_Terminal_01x02,J18,RS PRO Terminal Small x2,
230V - 6V,T1,RS PRO Transfo 6V 0.35VA,
Screw_Terminal_01x02,J13,RS PRO Terminal Small x2,
SS-10-15SPE,S14,RS PRO SS-10-15SPE,

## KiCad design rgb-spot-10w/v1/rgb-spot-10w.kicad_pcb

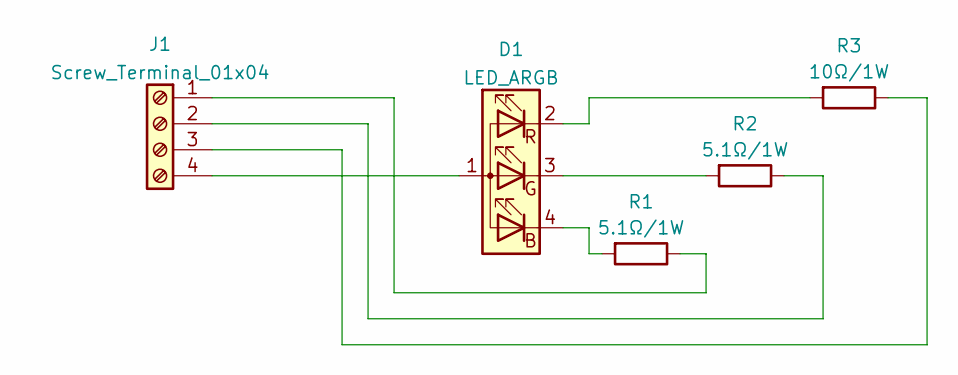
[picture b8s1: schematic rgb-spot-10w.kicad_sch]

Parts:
D1: LED_ARGB; LED RGB 10W
J1: Screw_Terminal_01x04; RS PRO Terminal Small x4
R1, R2: 5.1Ω/1W; R_2512_6332Metric; LCSC C514891
R3: 10Ω/1W; R_2512_6332Metric; LCSC C137014

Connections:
unnamed: D1.1 (A), J1.4
unnamed: D1.4 (BK), R1.2
unnamed: D1.3 (GK), R2.2
unnamed: D1.2 (RK), R3.2
unnamed: J1.1, R1.1
unnamed: J1.2, R2.1
unnamed: J1.3, R3.1

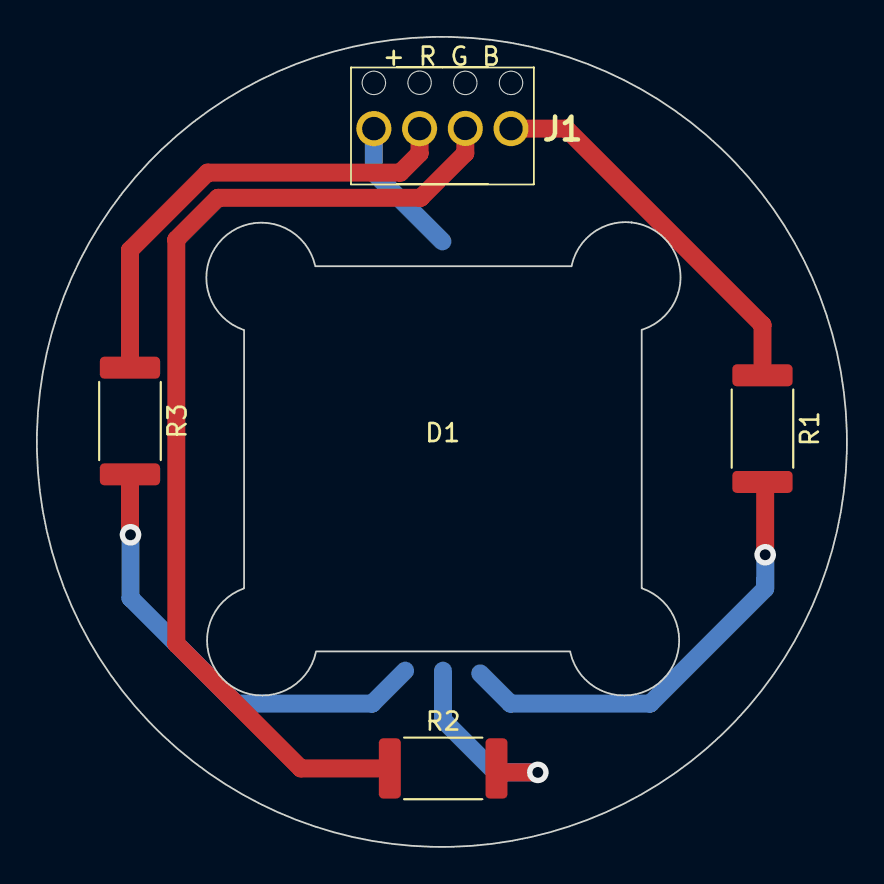
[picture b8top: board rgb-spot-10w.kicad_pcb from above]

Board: 2 copper layers, 45.0 x 45.0 mm, 5 parts (0 on the bottom side), 7 nets.

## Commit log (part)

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2022-12-31 clean library
2022-12-31 schematic wip
2022-12-31 annotate
2022-12-31 fix mosfet pinout
2022-12-31 wip schematic
2022-12-31 cleanup
2022-12-31 add switch
2022-12-31 restore switch drill diameter
2022-12-31 add small terminal footprint
2022-12-31 update TODO
2022-12-31 rotary switch
2023-01-01 update schematic
2023-01-01 update notes
2023-01-01 base pcb
2023-01-01 add borders
2023-01-01 wip tests
2023-01-01 update note
2023-01-01 update footprint
2023-01-01 wip tests pcb
2023-01-01 add CNMB pdf
2023-01-02 wip split controller
2023-01-02 schematic remove esp
2023-01-02 wip controller
2023-01-02 controller schematic
2023-01-02 update controller schematic
2023-01-02 enery monitor schematic
2023-01-02 wip pcb placement
2023-01-02 wip energy pcb
2023-01-02 wip pcb
2023-01-02 fix annotations
2023-01-02 pcb beta
2023-01-02 wip DRC
2023-01-02 add info
2023-01-03 fabrication files
2023-01-03 controller pcb placement
2023-01-03 controller pcb
2023-01-08 update 3dview
2023-01-08 add 3dview
2023-01-08 oops
2023-01-14 add test notes
2023-01-15 garden box presse etoupes
2023-02-04 update controller
2023-02-18 init v1.1
2023-02-18 fix pinouts
2023-02-18 wip fix pcb
2023-02-18 pcb placement
2023-02-18 wip pcb naming
2023-02-18 fix pcb
2023-02-18 update prod files
2023-02-18 add images
2023-02-19 rgb-box skeleton
2023-02-19 update ref spot
2023-02-20 update README + garden only
2023-02-21 convert to v7
2023-02-22 update rgb garden box
2023-02-24 update rgb box notes
2023-02-24 update organization + spot notes
2023-02-24 cosmetic
2023-02-25 update rgb spot notes
2023-02-25 add footprints
2023-02-25 fix layer + cut
2023-02-25 pcb OK
2023-02-25 add schematic
2023-02-25 fix footprint
2023-02-25 add production files
2023-02-28 update PCB R200 to 220
2023-03-09 mark GPIO0 (strapping pin) as unconnected on ESP32-POE
2023-03-09 rgb-garden-box wip schematic
2023-03-10 enclosing box layout
2023-03-10 update footprints for ESP32-POE
2023-03-10 DRC OK
2023-03-13 update presse etoupes
2023-03-18 switch IRLZ44N to TO220
2023-03-18 production files
2023-03-21 add pictures
2023-03-24 update pictures
2023-03-26 update bed smart plug
2023-04-07 add wiring
2023-04-22 add picture
2023-05-02 update list
2023-05-02 add garden box pictures
2023-05-02 test
2023-05-02 fix md layout
2023-05-05 Add potential projects
2023-05-07 add R&D garage door
2023-05-07 typo
2023-05-07 fix pictures layout
2023-05-10 update garage door driver readme
2023-05-14 energy monitor pics
2023-05-14 garage door add pics
2023-05-15 add energy pictures
2023-05-17 garage door R&D
2023-05-19 copy/paste schematic
2023-05-19 clean PCB + add edge cuts
2023-05-20 add wemos schematic/footprint library
2023-05-20 wip sch
2023-05-22 add ESP8266 strapping pins
2023-05-22 fix esp8366 used pins
2023-05-22 jlcpcb
2023-05-22 ajout ref borniers
2023-06-01 udpate README
2023-06-05 finalize
2023-06-05 add clim data
2023-06-05 add overflow pictures
2023-06-10 add toshiba notes
2023-06-20 add pcb size
2023-07-04 clim driver routing
2023-07-04 jlcpcb stuff
2023-07-04 3dview
2023-09-03 update pictures + notes clim driver
2023-09-07 Add clim-driver data
2023-09-07 Add wifi presence datra
2023-09-07 clim proto picture
2023-09-30 check
2023-09-30 layout
2023-10-16 update bed-smart-plug
2023-11-14 update project version
2023-11-14 proto1 wip schematic
2023-11-15 wip schematics
2023-11-15 update README/schematic
2023-11-15 fix symbols
2023-11-15 add footprint
2023-11-15 Recepteur 433Mhz
2023-11-15 update fusibles
2023-11-15 update heatsink
2023-11-15 jack
2023-11-15 Add DS18b20 ref
2023-11-15 Update C13/C14 plugs
2023-11-16 placement
2023-11-16 routing
2023-11-16 output files
2023-11-16 Add materiel
2023-11-16 Update materiel
2024-01-06 Add proto 1 schematic
2024-01-06 Add pinout
2024-01-06 add notes
2024-01-06 fix table
2024-01-06 cosmtic
2024-01-12 Add connectors stuff
2024-01-14 ajout écrous
2024-01-20 update observations proto 2
2024-01-20 update proto2
2024-01-20 update proto 3
2024-01-20 wip proto 3
2024-01-20 proto 3 wip
2024-01-21 update observations proto 1
2024-01-21 update todos proto3
2024-01-21 update PCB
2024-01-21 jlcpcb output proto3
2024-01-21 rework proto 3 edge cuts
2024-01-21 update pcb borders
2024-01-21 jlcpcb generate
2024-01-21 v1 schematic OK
2024-01-21 note
2024-01-27 wip pcb v1
2024-01-27 place components
2024-01-27 wip placement
2024-01-27 component placement
2024-01-27 wip routing
2024-01-27 generate jlcpcb parts
2024-01-27 jlcpcb order
2024-02-05 add notes v1
2024-03-08 add pic
2024-03-09 pictures + notes
2024-03-10 wip v1.1
2024-03-10 pcb size
2024-03-10 pics
2024-03-10 update moc3021 to available part
2024-03-14 gabarits
2024-03-15 add epanel controller debug ops
2024-03-19 add uart debug result
2024-03-20 update build images
2024-04-12 update remote data
2024-06-20 init rgb-led-inverter
2024-06-20 notes
2024-06-27 add note
2024-12-26 fairy lights
2024-12-26 heat driver skeleton
2024-12-27 update heater driver
2025-01-04 Add design notes
2025-01-04 add alims dimensions
2025-01-13 add notes proto 1
2025-01-18 init schematic
2025-01-19 add connector
2025-01-19 Add V1 skeleton
2025-01-19 fix schematic
2025-01-26 finish schematic + footprints
2025-02-08 Add heatsink
2025-02-09 routing + sign
2025-02-09 wiring
2025-02-09 jlcpcb gen
2025-06-16 materiel
2025-07-23 Add notes for epanelio v1.1
2025-08-23 Ajout doc construction gate-driver
2025-08-23 Ajout notes
2025-08-25 update fairylights
2025-09-14 Change RGB LED inverter status from question to stop
2025-09-14 Change RGB LED inverter status to 'no entry'
2026-02-04 Update README + deco-light
